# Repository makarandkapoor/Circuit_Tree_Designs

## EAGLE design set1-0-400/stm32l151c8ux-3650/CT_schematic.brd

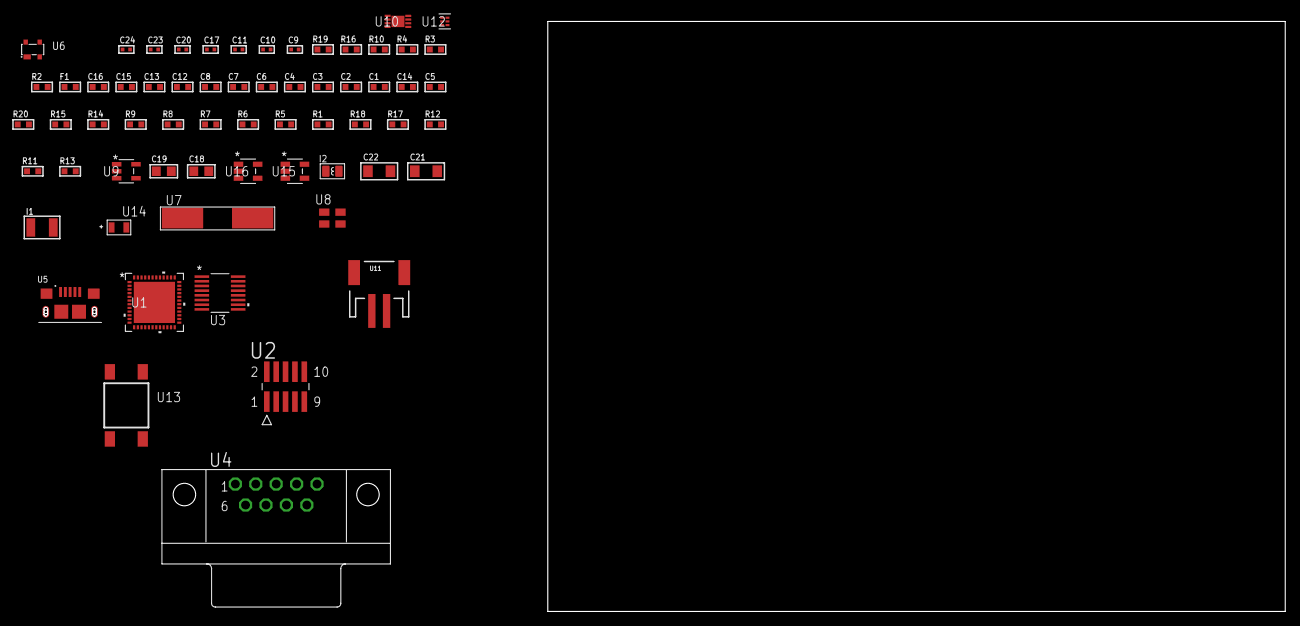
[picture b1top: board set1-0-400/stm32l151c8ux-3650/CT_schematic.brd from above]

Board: 2 copper layers, 168.3 x 80.0 mm, 63 parts (0 on the bottom side), 43 nets, no tracks yet.

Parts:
C1, C2, C3, C4, C6: 1e-07; C0603
C5: 4.7e-06; C0603
C7: 1e-08; C0603
C8, C12, C13, C15, C16: 1e-06; C0603
C9, C10: 1e-11; C0402
C11, C20: 1e-07; C0402
C14: 2.2e-07; C0603
C17, C23, C24: 1e-08; C0402
C18, C19: 1e-05; C0805
C21, C22: 1e-05; C1206
F1: 240.0; L0603
I1: 1e-05; L1210
I2: 3.3e-06; L0806
R1, R5, R6, R7, R8, R9, R14, R15, R20: 10000.0; R0603
R2: 1000.0; R0603
R3: 1600.5; R0603
R4: 4700.0; R0603
R10: 5.0; R0603
R11: 100000.0; R0603
R12: 220000.0; R0603
R13: 1000000.0; R0603
R16: 9100.0; R0603
R17: 680000.0; R0603
R18: 120000.0; R0603
R19: 2000.0; R0603
U1: STM32L151C8U6; UFQFPN48
U2: FTSH-105-01-L-DV-K; SAMTEC_FTSH-105-01-L-DV-K
U3: LTC2804CGN-1#PBF; SSOP-16
U4: 182-009-113R531; 182-009-MALE
U5: 10118193-0001LF; FCI_10118193-0001LF
U6: prtr5v0u2ax; SOT143B
U7: ABLS-25.000MHZ-B2F-T
U8: ASEK-32.768KHz-ECST; ASEK
U9: ltc3406es5; TSOT-23-5
U10: MCP73831T-2ACI/MC; DFN8_2X3MC
U11: S2B-PH-SM4-TB(LF)(SN); JST-2-SMD
U12: TPS3895ADRYR; SON-6
U13: 4-1437565-2; SW_4-1437565-2
U14: Q65110A2395; LGM67K-G1J2-24-Z
U15, U16: nc7sz125m5x; NC7SZ125M5X

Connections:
CLK_CRYSTAL_U1_5: C9.1, U1.5, U7.1
CLK_CRYSTAL_U1_6: C10.1, U1.6, U7.2
CLK_U1_3: U1.3, U8.3
GND: C1.2, C2.2, C3.2, C4.2, C5.2, C6.2, C7.2, C8.2, C9.2, C10.2, C11.2, C12.2, C13.2, C15.2, C16.2, C17.2, C18.2, C19.1, C19.2, C20.2, C21.2, C22.2, C23.2, C24.2, R2.2, R5.2, R9.2, R10.2, R12.2, R16.2, R18.2, R19.2, U1.8, U1.23, U1.35, U1.47, U1.49, U2.3, U2.5, U3.8, U4.5, U5.5, U5.6, U5.7, U5.8, U5.9, U6.1, U8.2, U9.2, U10.6, U10.9, U11.2, U12.2, U14.C, U15.2, U15.3, U16.1, U16.3
INPUT_USBPOWER_5V: C21.1, R20.2, U5.1, U6.4, U10.1, U10.2
NET_U1_1: C6.1, U1.1
NET_U1_7: R4.1, U1.7, U16.4
NET_U1_9: C7.1, C8.1, F1.1, U1.9
NET_U1_44: R5.1, U1.44
NET_U1_45: R3.1, U1.45, U14.A
NET_U1_46: R1.1, U1.46, U13.3, U13.4
NET_U2_9: R10.1, U2.9
NET_U3_6: C12.1, U3.6
NET_U3_7: C14.1, I1.2, U3.7
NET_U3_9: C13.1, U3.9
NET_U3_10: C14.2, U3.10
NET_U3_11: R11.1, U3.11
NET_U4_2: U3.1, U4.2
NET_U4_3: U3.3, U4.3
NET_U4_7: U3.2, U4.7
NET_U4_8: U3.4, U4.8
NET_U9_3: I2.1, U9.3
NET_U9_5: R12.1, R13.1, U9.5
NET_U9_ATNET_3: I2.2, R13.2
NET_U10_5: R20.1, U10.5
NET_U10_8: R19.1, U10.8
NET_U12_1: R15.1, R16.1, U12.1
NET_U12_3: R17.2, R18.1, U12.3
NET_U12_4: R14.1, U12.4, U15.4, U16.2
NET_U13_1: R2.1, U13.1, U13.2
PROC_SYS_JTCK_SWCLK: R9.1, U1.37, U2.4
PROC_SYS_JTDI: R7.1, U1.38, U2.8
PROC_SYS_JTDO_TRACESWO: U1.39, U2.6
PROC_SYS_JTMS_SWDIO: R8.1, U1.34, U2.2
PROC_USART2_CTS: U1.10, U3.13
PROC_USART2_RTS: U1.11, U3.15
PROC_USART2_RX: U1.13, U3.16
PROC_USART2_TX: U1.12, U3.14
PROC_USB_DM: U1.32, U5.2, U6.3
PROC_USB_DP: U1.33, U5.3, U6.2
RST_OUT_U2_JTAG_RST_B: R6.1, U2.10, U15.1
VCC_S1_3V7: C18.1, C22.1, U9.4, U10.3, U10.4, U11.1
VCC_TIER1_3V3: C1.1, C2.1, C3.1, C4.1, C5.1, C11.1, C15.1, C16.1, C17.1, C19.2, C20.1, C23.1, C24.1, F1.2, I1.1, I2.2, R1.2, R3.2, R4.2, R6.2, R7.2, R8.2, R11.2, R13.2, R14.2, R15.2, R17.1, U1.24, U1.36, U1.48, U2.1, U3.5, U3.12, U8.4, U12.6, U15.5, U16.5

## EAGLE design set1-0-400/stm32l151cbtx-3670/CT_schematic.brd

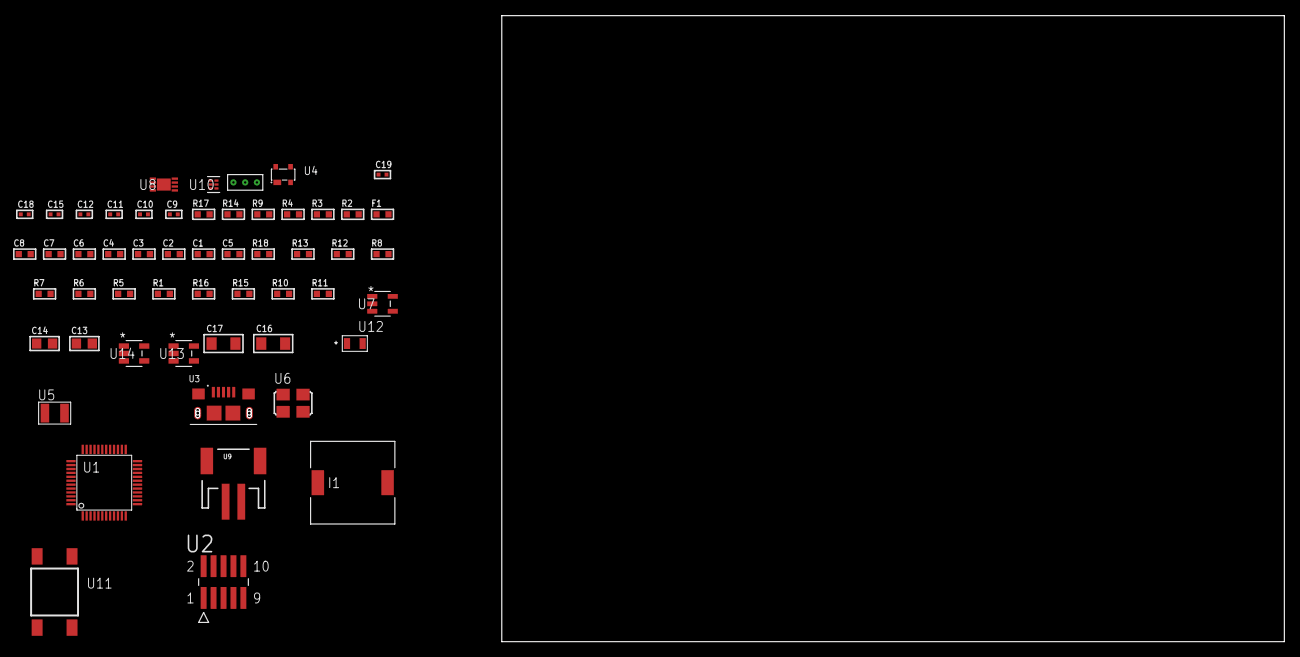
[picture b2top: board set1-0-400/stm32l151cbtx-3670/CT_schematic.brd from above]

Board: 2 copper layers, 54 parts (0 on the bottom side), 31 nets, no tracks yet.

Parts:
C1, C2, C3, C4, C6: 1e-07; C0603
C5: 4.7e-06; C0603
C7: 1e-08; C0603
C8: 1e-06; C0603
C9, C10: 1e-11; C0402
C11, C15: 1e-07; C0402
C12, C18, C19: 1e-08; C0402
C13, C14: 1e-05; C0805
C16, C17: 1e-05; C1206
F1: 240.0; L0603
I1: 3.8e-06; DR1040
R1, R5, R6, R7, R8, R12, R13, R18: 10000.0; R0603
R2: 1000.0; R0603
R3: 1600.5; R0603
R4: 4700.0; R0603
R9: 5.0; R0603
R10: 220000.0; R0603
R11: 1000000.0; R0603
R14: 9100.0; R0603
R15: 680000.0; R0603
R16: 120000.0; R0603
R17: 2000.0; R0603
U1: STM32L151CBT6; LQFP48
U2: FTSH-105-01-L-DV-K; SAMTEC_FTSH-105-01-L-DV-K
U3: 10118193-0001LF; FCI_10118193-0001LF
U4: prtr5v0u2ax; SOT143B
U5: ABS07-32.768KHZ-7-T
U6: ASFL1-25MHZ-NCS; ASFL1
U7: ltc3406es5; TSOT-23-5
U8: MCP73831T-2ACI/MC; DFN8_2X3MC
U9: S2B-PH-SM4-TB(LF)(SN); JST-2-SMD
U10: TPS3895ADRYR; SON-6
U11: 4-1437565-2; SW_4-1437565-2
U12: Q65110A2395; LGM67K-G1J2-24-Z
U13, U14: nc7sz125m5x; NC7SZ125M5X
U15: Dummy; DUMMY_PACKAGE_112

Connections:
CLK_CRYSTAL_U1_3: C9.1, U1.3, U5.1
CLK_CRYSTAL_U1_4: C10.1, U1.4, U5.2
CLK_U1_5: U1.5, U6.3
GND: C1.2, C2.2, C3.2, C4.2, C5.2, C6.2, C7.2, C8.2, C9.2, C10.2, C11.2, C12.2, C13.2, C14.1, C14.2, C15.2, C16.2, C17.2, C18.2, C19.2, R2.2, R5.2, R9.2, R10.2, R14.2, R16.2, R17.2, U1.8, U1.23, U1.35, U1.47, U2.3, U2.5, U3.5, U3.6, U3.7, U3.8, U3.9, U4.1, U6.2, U7.2, U8.6, U8.9, U9.2, U10.2, U12.C, U13.2, U13.3, U14.1, U14.3, U15.1
INPUT_USBPOWER_5V: C16.1, R18.2, U3.1, U4.4, U8.1, U8.2
NET_U1_1: C6.1, U1.1
NET_U1_7: R4.1, U1.7, U14.4
NET_U1_9: C7.1, C8.1, F1.1, U1.9
NET_U1_44: R5.1, U1.44
NET_U1_45: R3.1, U1.45, U12.A
NET_U1_46: R1.1, U1.46, U11.3, U11.4
NET_U2_9: R9.1, U2.9
NET_U7_3: I1.1, U7.3
NET_U7_5: R10.1, R11.1, U7.5
NET_U7_ATNET_3: I1.2, R11.2
NET_U8_5: R18.1, U8.5
NET_U8_8: R17.1, U8.8
NET_U10_1: R13.1, R14.1, U10.1
NET_U10_3: R15.2, R16.1, U10.3
NET_U10_4: R12.1, U10.4, U13.4, U14.2
NET_U11_1: R2.1, U11.1, U11.2
PROC_PC13_WKUP2: U1.2, U15.2
PROC_PH1_OSC_OUT: U1.6, U15.3
PROC_SYS_JTCK_SWCLK: R7.1, U1.37, U2.4
PROC_SYS_JTDO_TRACESWO: U1.39, U2.6
PROC_SYS_JTMS_SWDIO: R8.1, U1.34, U2.2
PROC_USB_DM: U1.32, U3.2, U4.3
PROC_USB_DP: U1.33, U3.3, U4.2
RST_OUT_U2_JTAG_RST_B: R6.1, U2.10, U13.1
VCC_S1_3V7: C13.1, C17.1, U7.4, U8.3, U8.4, U9.1
VCC_TIER1_3V3: C1.1, C2.1, C3.1, C4.1, C5.1, C11.1, C12.1, C14.2, C15.1, C18.1, C19.1, F1.2, I1.2, R1.2, R3.2, R4.2, R6.2, R7.2, R8.2, R11.2, R12.2, R13.2, R15.1, U1.24, U1.36, U1.48, U2.1, U6.4, U10.6, U13.5, U14.5

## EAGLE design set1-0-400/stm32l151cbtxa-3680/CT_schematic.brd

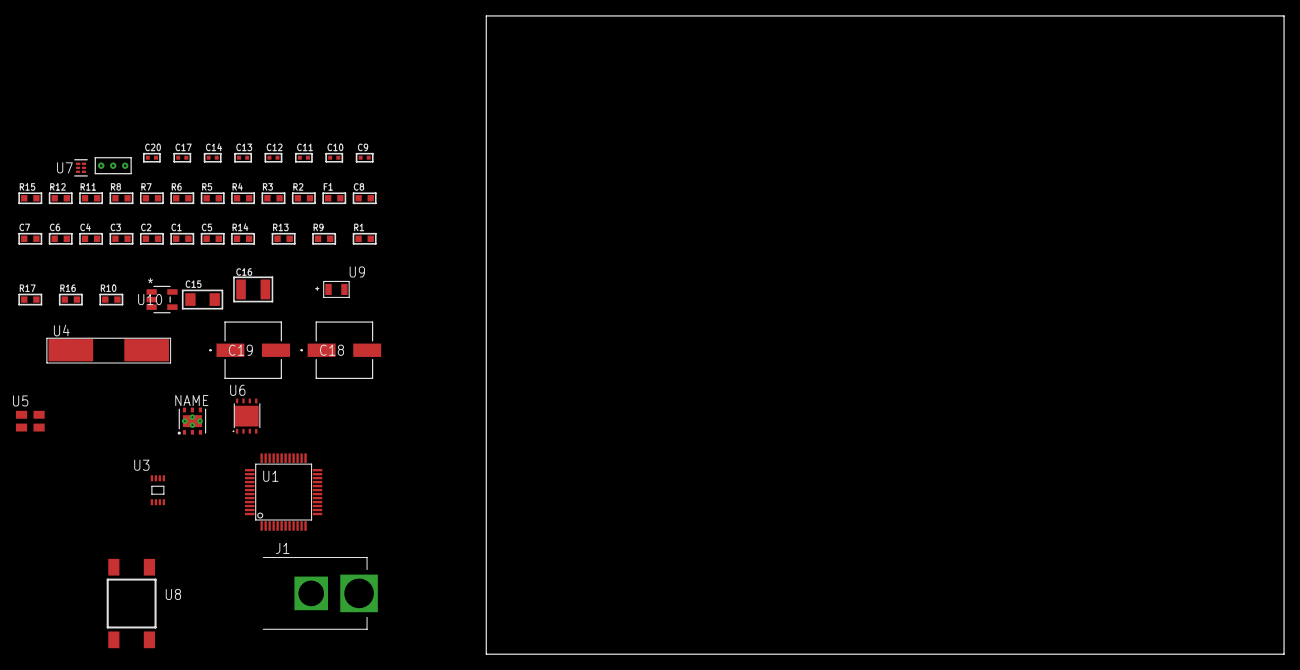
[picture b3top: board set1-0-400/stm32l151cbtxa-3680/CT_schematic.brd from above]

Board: 2 copper layers, 100.0 x 80.0 mm, 50 parts (0 on the bottom side), 25 nets, no tracks yet.

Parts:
C1, C2, C3, C4, C6: 1e-07; C0603
C5: 4.7e-06; C0603
C7: 1e-08; C0603
C8: 1e-06; C0603
C9, C10: 1e-11; C0402
C11, C12, C13, C14, C20: 1e-08; C0402
C15: 1e-05; C1206
C16: 1e-05; C1210
C17: 1e-07; C0402
C18, C19: 0.0001; EXV-9H
F1: 240.0; L0603
J1: PJ-037B; PJ-037B_PACKAGE
R1, R9, R13, R14: 10000.0; R0603
R2, R12: 1000.0; R0603
R3: 1600.5; R0603
R4: 4700.0; R0603
R5, R6, R7, R8: 2200.0; R0603
R10: 100000.0; R0603
R11: 2231.0; R0603
R15: 9100.0; R0603
R16: 680000.0; R0603
R17: 120000.0; R0603
U1: STM32L151CBT6A; LQFP48
U2: HDC1080DMBR; WSON-6
U3: 24AA08T-I/MNY; TDFN-8/6MM
U4: ABLS-25.000MHZ-B2F-T
U5: ASEK-32.768KHz-ECST; ASEK
U6: LP3878SDX-ADJ/NOPB; WSON-8
U7: TPS3895ADRYR; SON-6
U8: 4-1437565-2; SW_4-1437565-2
U9: Q65110A2395; LGM67K-G1J2-24-Z
U10: nc7sz125m5x; NC7SZ125M5X
U11: Dummy; DUMMY_PACKAGE_103

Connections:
CLK_CRYSTAL_U1_5: C9.1, U1.5, U4.1
CLK_CRYSTAL_U1_6: C10.1, U1.6, U4.2
CLK_U1_3: U1.3, U5.3
GND: C1.2, C2.2, C3.2, C4.2, C5.2, C6.2, C7.2, C8.2, C9.2, C10.2, C11.2, C12.2, C13.2, C14.2, C15.2, C16.2, C17.2, C18.2, C19.2, C20.2, J1.2, R2.2, R9.2, R12.2, R15.2, R17.2, U1.8, U1.23, U1.35, U1.47, U2.2, U2.PAD, U3.4, U3.7, U5.2, U6.3, U6.PAD, U7.2, U9.C, U10.1, U10.3, U11.1
NET_U1_1: C6.1, U1.1
NET_U1_7: R4.1, U1.7, U10.4
NET_U1_9: C7.1, C8.1, F1.1, U1.9
NET_U1_21: R7.1, U1.21, U3.6
NET_U1_22: R8.1, U1.22, U3.5
NET_U1_42: R5.1, U1.42, U2.6
NET_U1_43: R6.1, U1.43, U2.1
NET_U1_44: R9.1, U1.44
NET_U1_45: R3.1, U1.45, U9.A
NET_U1_46: R1.1, U1.46, U8.3, U8.4
NET_U6_1: C14.1, U6.1
NET_U6_6: R11.2, R12.1, U6.6
NET_U6_8: R10.1, U6.8
NET_U7_1: R14.1, R15.1, U7.1
NET_U7_3: R16.2, R17.1, U7.3
NET_U7_4: R13.1, U7.4, U10.2
NET_U8_1: R2.1, U8.1, U8.2
PROC_TIM10_CH1: U1.16, U11.2
PROC_TIM11_CH1: U1.17, U11.3
VCC_S1_9V1: C15.1, C18.1, C19.1, J1.1, R10.2, U6.4
VCC_TIER1_3V3: C1.1, C2.1, C3.1, C4.1, C5.1, C11.1, C12.1, C13.1, C16.1, C17.1, C20.1, F1.2, R1.2, R3.2, R4.2, R5.2, R6.2, R7.2, R8.2, R11.1, R13.2, R14.2, R16.1, U1.24, U1.36, U1.48, U2.5, U3.8, U5.4, U6.5, U7.6, U10.5

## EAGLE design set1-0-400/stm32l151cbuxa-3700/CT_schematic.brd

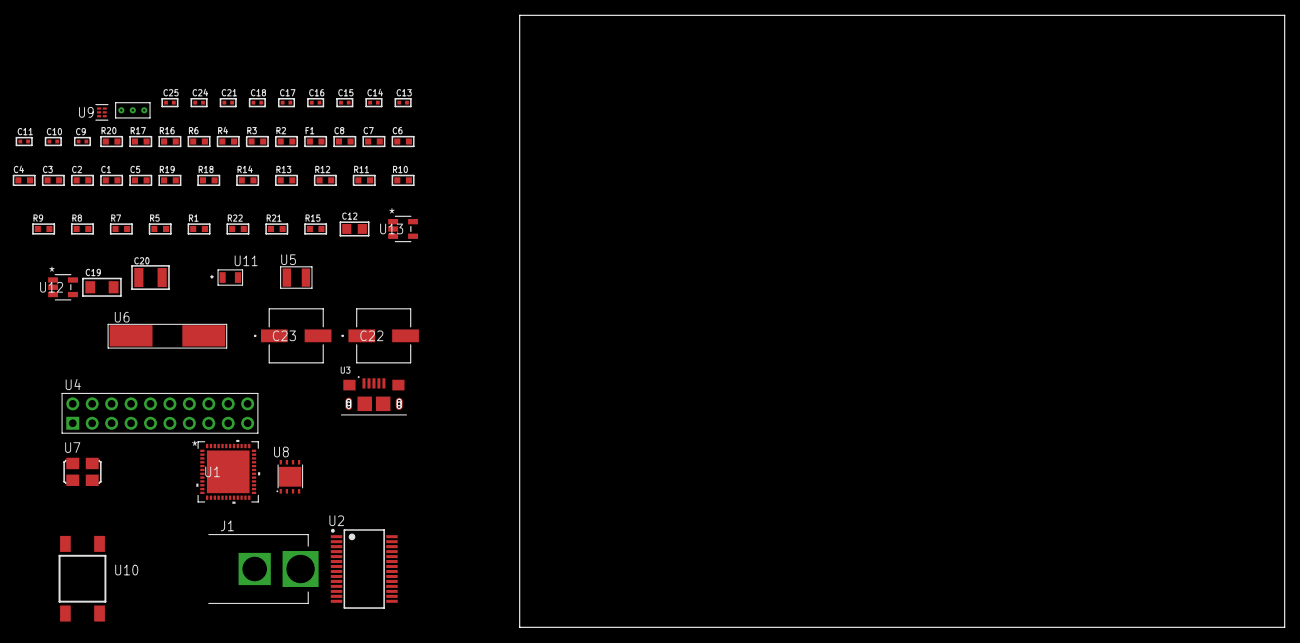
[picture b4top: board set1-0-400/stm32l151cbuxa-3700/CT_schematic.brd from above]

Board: 2 copper layers, 122.6 x 80.0 mm, 63 parts (0 on the bottom side), 40 nets, no tracks yet.

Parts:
C1, C2, C3, C4, C6: 1e-07; C0603
C5: 4.7e-06; C0603
C7: 1e-08; C0603
C8: 1e-06; C0603
C9, C10: 1e-11; C0402
C11, C13, C14, C15, C16, C21: 1e-07; C0402
C12: 4.7e-06; C0805
C17, C18, C24, C25: 1e-08; C0402
C19: 1e-05; C1206
C20: 1e-05; C1210
C22, C23: 0.0001; EXV-9H
F1: 240.0; L0603
J1: PJ-037B; PJ-037B_PACKAGE
R1, R5, R7, R8, R9, R10, R11, R12, R13, R14, R18, R19: 10000.0; R0603
R2, R17: 1000.0; R0603
R3: 1600.5; R0603
R4, R6: 4700.0; R0603
R15: 100000.0; R0603
R16: 2231.0; R0603
R20: 9100.0; R0603
R21: 680000.0; R0603
R22: 120000.0; R0603
U1: STM32L151CBU6A; UFQFPN48
U2: FT232RL-REEL; SSOP-28
U3: 10118193-0001LF; FCI_10118193-0001LF
U4: TST-110-05-T-D-RA
U5: ABS07-32.768KHZ-7-T
U6: ABLS-12.000MHZ-B4-T
U7: ASFL1-25MHZ-NCS; ASFL1
U8: LP3878SDX-ADJ/NOPB; WSON-8
U9: TPS3895ADRYR; SON-6
U10: 4-1437565-2; SW_4-1437565-2
U11: Q65110A2395; LGM67K-G1J2-24-Z
U12, U13: nc7sz125m5x; NC7SZ125M5X
U14: Dummy; DUMMY_PACKAGE_130

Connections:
CLK_CRYSTAL_U1_3: C9.1, U1.3, U5.1
CLK_CRYSTAL_U1_4: C10.1, U1.4, U5.2
CLK_CRYSTAL_U2_27: U2.27, U6.1
CLK_CRYSTAL_U2_28: U2.28, U6.2
CLK_U1_5: U1.5, U7.3
GND: C1.2, C2.2, C3.2, C4.2, C5.2, C6.2, C7.2, C8.2, C9.2, C10.2, C11.2, C12.2, C13.2, C14.2, C15.2, C16.2, C17.2, C18.2, C19.2, C20.2, C21.2, C22.2, C23.2, C24.2, C25.2, J1.2, R2.2, R5.2, R8.2, R14.2, R17.2, R20.2, R22.2, U1.8, U1.23, U1.35, U1.47, U1.49, U2.7, U2.18, U2.21, U2.25, U2.26, U3.5, U3.6, U3.7, U3.8, U3.9, U4.4, U4.6, U4.8, U4.10, U4.12, U4.14, U4.16, U4.18, U4.20, U7.2, U8.3, U8.PAD, U9.2, U11.C, U12.2, U12.3, U13.1, U13.3, U14.1
NET_U1_1: C6.1, U1.1
NET_U1_7: R4.1, U1.7, U13.4
NET_U1_9: C7.1, C8.1, F1.1, U1.9
NET_U1_44: R5.1, U1.44
NET_U1_45: R3.1, U1.45, U11.A
NET_U1_46: R1.1, U1.46, U10.3, U10.4
NET_U2_14: R7.1, U2.14
NET_U2_17: C13.1, U2.17
NET_U2_19: R8.1, U2.19
NET_U3_1: R6.1, U3.1
NET_U3_2: U2.16, U3.2
NET_U3_3: U2.15, U3.3
NET_U4_19: R14.1, U4.19
NET_U8_1: C18.1, U8.1
NET_U8_6: R16.2, R17.1, U8.6
NET_U8_8: R15.1, U8.8
NET_U9_1: R19.1, R20.1, U9.1
NET_U9_3: R21.2, R22.1, U9.3
NET_U9_4: R18.1, U9.4, U12.4, U13.2
NET_U10_1: R2.1, U10.1, U10.2
PROC_ADC_IN19: U1.26, U14.3
PROC_ADC_IN20: U1.27, U14.2
PROC_SYS_JTCK_SWCLK: R12.1, U1.37, U4.9
PROC_SYS_JTDI: R10.1, U1.38, U4.5
PROC_SYS_JTDO_TRACESWO: U1.39, U4.13
PROC_SYS_JTMS_SWDIO: R11.1, U1.34, U4.7
PROC_SYS_JTRST: R9.1, U1.40, U4.3
PROC_USART1_CTS: U1.32, U2.3
PROC_USART1_RTS: U1.33, U2.11
PROC_USART1_RX: U1.31, U2.1
PROC_USART1_TX: U1.30, U2.5
RST_OUT_U4_SRESET_B: R13.1, U4.15, U12.1
VCC_S1_8V5: C19.1, C22.1, C23.1, J1.1, R15.2, U8.4
VCC_TIER1_3V3: C1.1, C2.1, C3.1, C4.1, C5.1, C11.1, C12.1, C14.1, C15.1, C16.1, C17.1, C20.1, C21.1, C24.1, C25.1, F1.2, R1.2, R3.2, R4.2, R7.2, R9.2, R10.2, R11.2, R12.2, R13.2, R16.1, R18.2, R19.2, R21.1, U1.24, U1.36, U1.48, U2.4, U2.20, U4.1, U4.2, U7.4, U8.5, U9.6, U12.5, U13.5

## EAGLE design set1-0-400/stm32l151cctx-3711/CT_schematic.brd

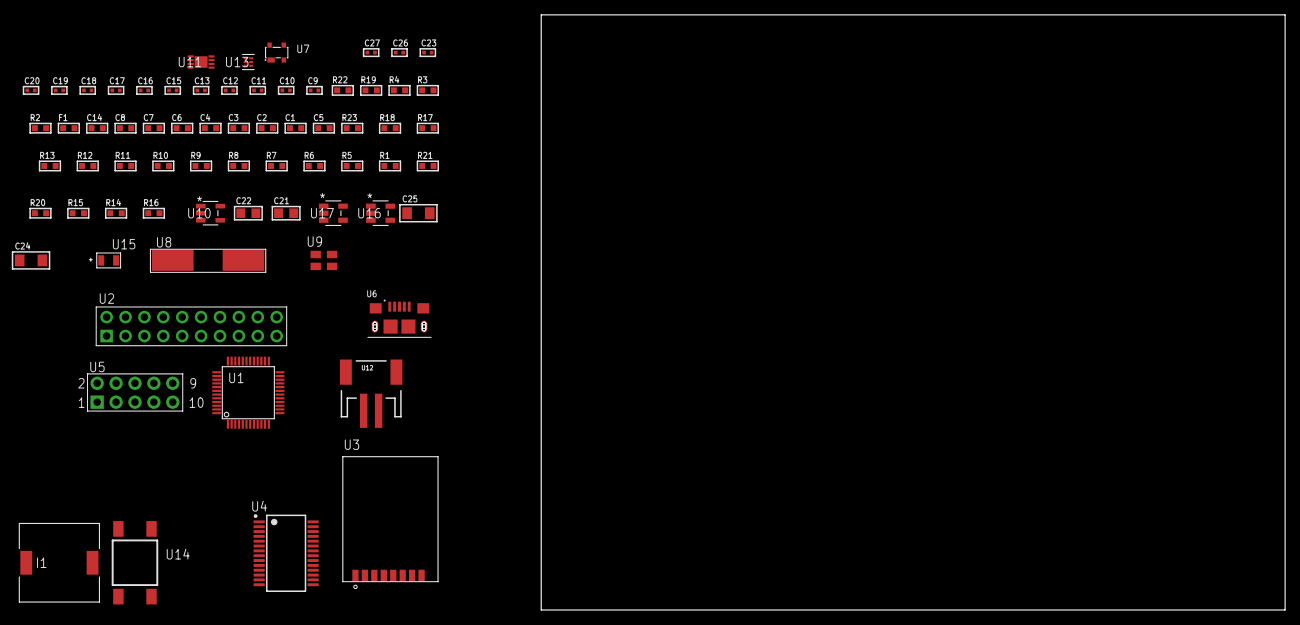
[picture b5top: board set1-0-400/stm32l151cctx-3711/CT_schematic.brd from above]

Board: 2 copper layers, 122.6 x 80.0 mm, 69 parts (0 on the bottom side), 51 nets, no tracks yet.

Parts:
C1, C2, C3, C4, C6: 1e-07; C0603
C5: 4.7e-06; C0603
C7: 1e-08; C0603
C8, C14: 1e-06; C0603
C9, C10: 1e-11; C0402
C11, C12, C13, C15, C16, C17, C18, C19, C23: 1e-07; C0402
C20, C26, C27: 1e-08; C0402
C21, C22: 1e-05; C0805
C24, C25: 1e-05; C1206
F1: 240.0; L0603
I1: 2.5e-06; DR1040
R1, R5, R6, R7, R8, R9, R10, R11, R12, R13, R17, R18, R23: 10000.0; R0603
R2: 1000.0; R0603
R3: 1600.5; R0603
R4: 4700.0; R0603
R14: 100000.0; R0603
R15: 220000.0; R0603
R16: 1000000.0; R0603
R19: 9100.0; R0603
R20: 680000.0; R0603
R21: 120000.0; R0603
R22: 2000.0; R0603
U1: STM32L151CCT6; LQFP48
U2: TST-110-05-T-D-RA
U3: RFM75-S
U4: ST3241EBPR; SSOP-28
U5: HTSS-105-01-G-D
U6: 10118193-0001LF; FCI_10118193-0001LF
U7: prtr5v0u2ax; SOT143B
U8: ABLS-25.000MHZ-B2F-T
U9: ASEK-32.768KHz-ECST; ASEK
U10: ltc3406es5; TSOT-23-5
U11: MCP73831T-2ACI/MC; DFN8_2X3MC
U12: S2B-PH-SM4-TB(LF)(SN); JST-2-SMD
U13: TPS3895ADRYR; SON-6
U14: 4-1437565-2; SW_4-1437565-2
U15: Q65110A2395; LGM67K-G1J2-24-Z
U16, U17: nc7sz125m5x; NC7SZ125M5X

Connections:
CLK_CRYSTAL_U1_5: C9.1, U1.5, U8.1
CLK_CRYSTAL_U1_6: C10.1, U1.6, U8.2
CLK_U1_3: U1.3, U9.3
GND: C1.2, C2.2, C3.2, C4.2, C5.2, C6.2, C7.2, C8.2, C9.2, C10.2, C11.2, C12.2, C13.2, C14.2, C15.2, C18.2, C19.2, C20.2, C21.2, C22.1, C22.2, C23.2, C24.2, C25.2, C26.2, C27.2, R2.2, R5.2, R11.2, R15.2, R19.2, R21.2, R22.2, U1.8, U1.23, U1.35, U1.47, U2.4, U2.6, U2.8, U2.10, U2.12, U2.14, U2.16, U2.18, U2.20, U3.1, U4.23, U4.25, U5.9, U6.5, U6.6, U6.7, U6.8, U6.9, U7.1, U9.2, U10.2, U11.6, U11.9, U12.2, U13.2, U15.C, U16.2, U16.3, U17.1, U17.3
INPUT_USBPOWER_5V: C24.1, R23.2, U6.1, U7.4, U11.1, U11.2
NET_U1_1: C6.1, U1.1
NET_U1_7: R4.1, U1.7, U17.4
NET_U1_9: C7.1, C8.1, F1.1, U1.9
NET_U1_44: R5.1, U1.44
NET_U1_45: R3.1, U1.45, U15.A
NET_U1_46: R1.1, U1.46, U14.3, U14.4
NET_U2_19: R11.1, U2.19
NET_U3_3: R12.1, U3.3
NET_U4_1: C17.1, U4.1
NET_U4_2: C17.2, U4.2
NET_U4_3: C19.1, U4.3
NET_U4_22: R14.1, U4.22
NET_U4_24: C16.2, U4.24
NET_U4_27: C18.1, U4.27
NET_U4_28: C16.1, U4.28
NET_U5_3: U4.4, U5.3
NET_U5_4: U4.5, U5.4
NET_U5_5: U4.9, U5.5
NET_U5_6: U4.10, U5.6
NET_U10_3: I1.1, U10.3
NET_U10_5: R15.1, R16.1, U10.5
NET_U10_ATNET_3: I1.2, R16.2
NET_U11_5: R23.1, U11.5
NET_U11_8: R22.1, U11.8
NET_U13_1: R18.1, R19.1, U13.1
NET_U13_3: R20.2, R21.1, U13.3
NET_U13_4: R17.1, U13.4, U16.4, U17.2
NET_U14_1: R2.1, U14.1, U14.2
PROC_SPI1_MISO: U1.16, U3.7
PROC_SPI1_MOSI: U1.17, U3.6
PROC_SPI1_NSS: R13.1, U1.14, U3.4
PROC_SPI1_SCK: U1.15, U3.5
PROC_SYS_JTCK_SWCLK: R9.1, U1.37, U2.9
PROC_SYS_JTDI: R7.1, U1.38, U2.5
PROC_SYS_JTDO_TRACESWO: U1.39, U2.13
PROC_SYS_JTMS_SWDIO: R8.1, U1.34, U2.7
PROC_SYS_JTRST: R6.1, U1.40, U2.3
PROC_USART2_CTS: U1.10, U4.13
PROC_USART2_RTS: U1.11, U4.18
PROC_USART2_RX: U1.13, U4.19
PROC_USART2_TX: U1.12, U4.14
PROC_USB_DM: U1.32, U6.2, U7.3
PROC_USB_DP: U1.33, U6.3, U7.2
RST_OUT_U2_SRESET_B: R10.1, U2.15, U16.1
VCC_S1_3V7: C21.1, C25.1, U10.4, U11.3, U11.4, U12.1
VCC_TIER1_3V3: C1.1, C2.1, C3.1, C4.1, C5.1, C11.1, C12.1, C13.1, C14.1, C15.1, C20.1, C22.2, C23.1, C26.1, C27.1, F1.2, I1.2, R1.2, R3.2, R4.2, R6.2, R7.2, R8.2, R9.2, R10.2, R12.2, R13.2, R14.2, R16.2, R17.2, R18.2, R20.1, U1.24, U1.36, U1.48, U2.1, U2.2, U3.2, U4.26, U9.4, U13.6, U16.5, U17.5

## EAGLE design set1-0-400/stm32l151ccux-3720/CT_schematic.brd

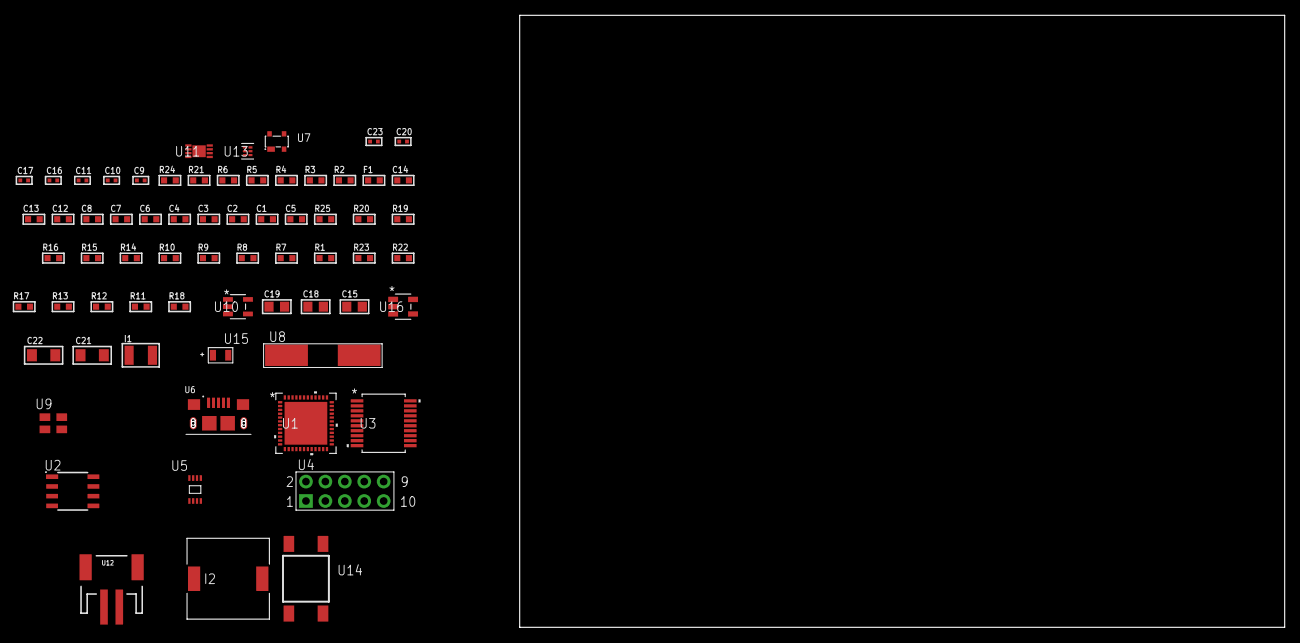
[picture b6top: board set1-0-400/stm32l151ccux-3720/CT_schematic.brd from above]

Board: 2 copper layers, 67 parts (0 on the bottom side), 51 nets, no tracks yet.

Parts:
C1, C2, C3, C4, C6: 1e-07; C0603
C5: 4.7e-06; C0603
C7: 1e-08; C0603
C8, C12, C13, C14: 1e-06; C0603
C9, C10: 1e-11; C0402
C11, C16, C17, C23: 1e-08; C0402
C15: 4.7e-06; C0805
C18, C19: 1e-05; C0805
C20: 1e-07; C0402
C21, C22: 1e-05; C1206
F1: 240.0; L0603
I1: 1.5e-05; L1210
I2: 2.5e-06; DR1040
R1, R7, R8, R9, R10, R14, R15, R16, R19, R20, R25: 10000.0; R0603
R2: 1000.0; R0603
R3: 1600.5; R0603
R4: 4700.0; R0603
R5, R6: 2200.0; R0603
R11, R12, R13: 100000.0; R0603
R17: 220000.0; R0603
R18: 1000000.0; R0603
R21: 9100.0; R0603
R22: 680000.0; R0603
R23: 120000.0; R0603
R24: 2000.0; R0603
U1: STM32L151CCU6; UFQFPN48
U2: AT25020B-SSHL-T; SOIC-8
U3: MAX3218EAP+T; SSOP-20
U4: HTSS-105-01-G-D
U5: 24AA32AT-I/MNY; TDFN-8/6MM
U6: 10118193-0001LF; FCI_10118193-0001LF
U7: prtr5v0u2ax; SOT143B
U8: ABLS-25.000MHZ-B2F-T
U9: ASEK-32.768KHz-ECST; ASEK
U10: ltc3406es5; TSOT-23-5
U11: MCP73831T-2ACI/MC; DFN8_2X3MC
U12: S2B-PH-SM4-TB(LF)(SN); JST-2-SMD
U13: TPS3895ADRYR; SON-6
U14: 4-1437565-2; SW_4-1437565-2
U15: Q65110A2395; LGM67K-G1J2-24-Z
U16: nc7sz125m5x; NC7SZ125M5X

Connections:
CLK_CRYSTAL_U1_5: C9.1, U1.5, U8.1
CLK_CRYSTAL_U1_6: C10.1, U1.6, U8.2
CLK_U1_3: U1.3, U9.3
GND: C1.2, C2.2, C3.2, C4.2, C5.2, C6.2, C7.2, C8.2, C9.2, C10.2, C11.2, C12.2, C13.2, C14.2, C16.2, C17.2, C18.2, C19.1, C19.2, C20.2, C21.2, C22.2, C23.2, R2.2, R7.2, R14.2, R17.2, R21.2, R23.2, R24.2, U1.8, U1.23, U1.35, U1.47, U1.49, U2.4, U3.5, U3.17, U3.20, U4.9, U5.4, U6.5, U6.6, U6.7, U6.8, U6.9, U7.1, U9.2, U10.2, U11.6, U11.9, U12.2, U13.2, U15.C, U16.1, U16.3
INPUT_USBPOWER_5V: C21.1, R25.2, U6.1, U7.4, U11.1, U11.2
NET_U1_1: C6.1, U1.1
NET_U1_7: R4.1, U1.7, U16.4
NET_U1_9: C7.1, C8.1, F1.1, U1.9
NET_U1_42: R5.1, U1.42, U5.6
NET_U1_43: R6.1, U1.43, U5.5
NET_U1_44: R7.1, U1.44
NET_U1_45: R3.1, U1.45, U15.A
NET_U1_46: R1.1, U1.46, U14.3, U14.4
NET_U2_3: R8.1, U2.3
NET_U2_7: R10.1, U2.7
NET_U3_1: I1.1, U3.1
NET_U3_2: R11.1, U3.2
NET_U3_3: R12.1, U3.3
NET_U3_4: R13.1, U3.4
NET_U3_15: C14.1, U3.15
NET_U3_16: C15.2, U3.16
NET_U3_18: C15.1, U3.18
NET_U3_19: C13.1, U3.19
NET_U4_3: U3.12, U4.3
NET_U4_4: U3.11, U4.4
NET_U4_5: U3.14, U4.5
NET_U4_6: U3.13, U4.6
NET_U5_1: R14.1, U5.1
NET_U5_2: R15.1, U5.2
NET_U5_3: R16.1, U5.3
NET_U10_3: I2.1, U10.3
NET_U10_5: R17.1, R18.1, U10.5
NET_U10_ATNET_3: I2.2, R18.2
NET_U11_5: R25.1, U11.5
NET_U11_8: R24.1, U11.8
NET_U13_1: R20.1, R21.1, U13.1
NET_U13_3: R22.2, R23.1, U13.3
NET_U13_4: R19.1, U13.4, U16.2
NET_U14_1: R2.1, U14.1, U14.2
PROC_SPI1_MISO: U1.16, U2.2
PROC_SPI1_MOSI: U1.17, U2.5
PROC_SPI1_NSS: R9.1, U1.14, U2.1
PROC_SPI1_SCK: U1.15, U2.6
PROC_USART2_CTS: U1.10, U3.8
PROC_USART2_RTS: U1.11, U3.10
PROC_USART2_RX: U1.13, U3.9
PROC_USART2_TX: U1.12, U3.7
PROC_USB_DM: U1.32, U6.2, U7.3
PROC_USB_DP: U1.33, U6.3, U7.2
VCC_S1_3V7: C18.1, C22.1, U10.4, U11.3, U11.4, U12.1
VCC_TIER1_3V3: C1.1, C2.1, C3.1, C4.1, C5.1, C11.1, C12.1, C16.1, C17.1, C19.2, C20.1, C23.1, F1.2, I1.2, I2.2, R1.2, R3.2, R4.2, R5.2, R6.2, R8.2, R9.2, R10.2, R11.2, R12.2, R13.2, R15.2, R16.2, R18.2, R19.2, R20.2, R22.1, U1.24, U1.36, U1.48, U2.8, U3.6, U5.7, U5.8, U9.4, U13.6, U16.5

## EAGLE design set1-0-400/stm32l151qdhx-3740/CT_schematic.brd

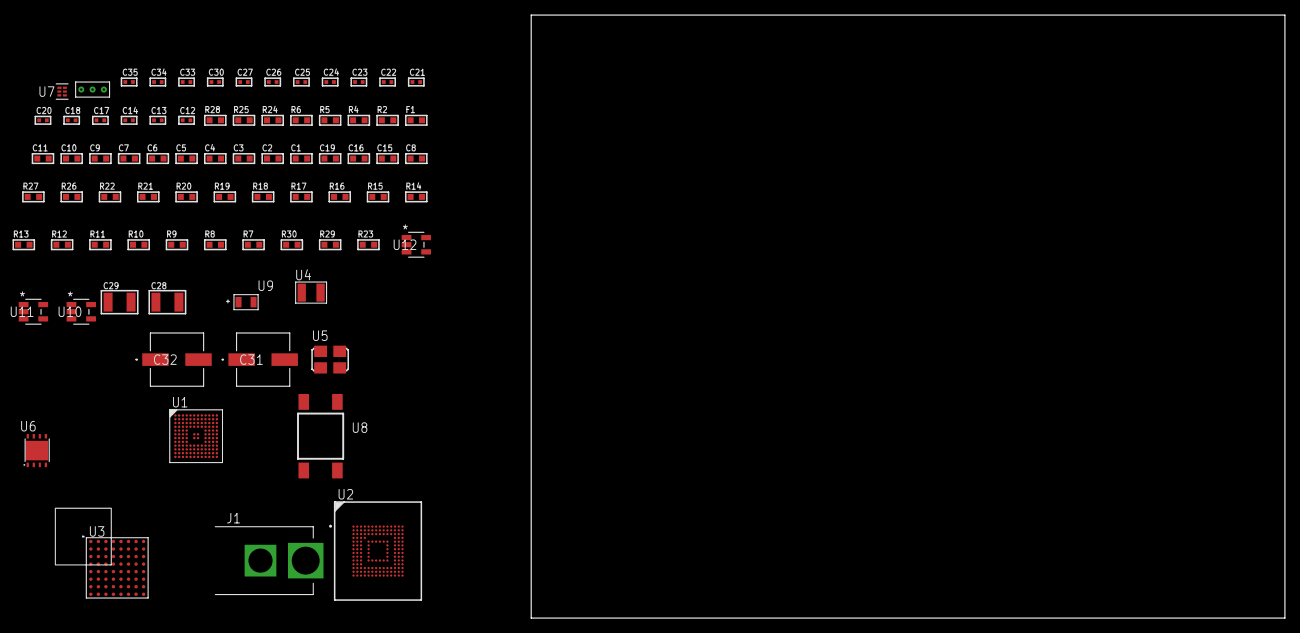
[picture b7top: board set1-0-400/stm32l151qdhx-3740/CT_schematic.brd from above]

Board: 2 copper layers, 100.0 x 80.0 mm, 78 parts (0 on the bottom side), 71 nets, no tracks yet.

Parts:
C1, C2, C3, C4, C5, C6, C7, C9: 1e-07; C0603
C8: 4.7e-06; C0603
C10: 1e-08; C0603
C11: 1e-06; C0603
C12, C13: 1e-11; C0402
C14, C17, C18, C20, C22, C24, C30: 1e-07; C0402
C15, C16, C19: 2.2e-06; C0603
C21, C23, C25, C26, C27, C33, C34, C35: 1e-08; C0402
C28, C29: 1e-05; C1210
C31, C32: 0.0001; EXV-9H
F1: 240.0; L0603
J1: PJ-037B; PJ-037B_PACKAGE
R2, R25: 1000.0; R0603
R4, R5, R6: 4700.0; R0603
R7, R18, R19, R20, R21, R22, R26, R27: 10000.0; R0603
R8, R9, R10, R11, R12, R13, R14, R15, R16, R17: 34000.0; R0603
R23: 100000.0; R0603
R24: 2231.0; R0603
R28: 9100.0; R0603
R29: 680000.0; R0603
R30: 120000.0; R0603
U1: STM32L151QDH6; UFBGA132
U2: mtfc4gmcdm; TFBGA-153
U3: PC28F512P33BFD
U4: ABS07-32.768KHZ-7-T
U5: ASFL1-25MHZ-NCS; ASFL1
U6: LP3878SDX-ADJ/NOPB; WSON-8
U7: TPS3895ADRYR; SON-6
U8: 4-1437565-2; SW_4-1437565-2
U9: Q65110A2395; LGM67K-G1J2-24-Z
U10, U11, U12: nc7sz125m5x; NC7SZ125M5X
U13: Dummy; DUMMY_PACKAGE_176

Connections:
CLK_CRYSTAL_U1_D1: C12.1, U1.D1, U4.1
CLK_CRYSTAL_U1_E1: C13.1, U1.E1, U4.2
CLK_U1_F1: U1.F1, U5.3
GND: C1.2, C2.2, C3.2, C4.2, C5.2, C6.2, C7.2, C8.2, C9.2, C10.2, C11.2, C12.2, C13.2, C14.2, C15.2, C16.2, C17.2, C18.2, C19.2, C20.2, C21.2, C22.2, C23.2, C24.2, C25.2, C26.2, C27.2, C28.2, C29.2, C30.2, C31.2, C32.2, C33.2, C34.2, C35.2, J1.2, R2.2, R7.2, R25.2, R28.2, R30.2, U1.D3, U1.E3, U1.F2, U1.F6, U1.F7, U1.F11, U1.F12, U1.J1, U2.C4, U2.E7, U2.G5, U2.H10, U2.K8, U2.N2, U2.N5, U2.P4, U2.P6, U3.B2, U3.H2, U3.H4, U3.H6, U5.2, U6.3, U6.PAD, U7.2, U9.C, U10.1, U10.3, U11.1, U11.3, U12.1, U12.3, U13.1
NET_U1_A4: R7.1, U1.A4
NET_U1_E2: C9.1, U1.E2
NET_U1_H2: R6.1, U1.H2, U12.4
NET_U1_M1: C10.1, C11.1, F1.1, U1.L1, U1.M1
NET_U1_M6: U8.3, U8.4
NET_U2_C2: C16.1, C17.1, U2.C2
NET_U2_K5: R4.1, U2.K5, U10.4
NET_U3_A4: C24.1, C25.1, U3.A4
NET_U3_C6: R21.1, U3.C6
NET_U3_D4: R5.1, U3.D4, U11.4
NET_U6_1: C27.1, U6.1
NET_U6_6: R24.2, R25.1, U6.6
NET_U6_8: R23.1, U6.8
NET_U7_1: R27.1, R28.1, U7.1
NET_U7_3: R29.2, R30.1, U7.3
NET_U7_4: R26.1, U7.4, U10.2, U11.2, U12.2
NET_U8_1: R2.1, U8.1, U8.2
PROC_ADC_IN20: U1.K11, U13.2
PROC_ADC_IN28: U1.G4, U13.3
PROC_FSMC_A6: U1.J7, U3.C2
PROC_FSMC_A7: U1.K7, U3.A3
PROC_FSMC_A8: U1.J8, U3.B3
PROC_FSMC_A9: U1.J9, U3.C3
PROC_FSMC_A10: U1.H9, U3.D3
PROC_FSMC_A11: U1.G9, U3.C4
PROC_FSMC_A12: U1.G10, U3.A5
PROC_FSMC_A13: U1.F9, U3.B5
PROC_FSMC_A14: U1.F10, U3.C5
PROC_FSMC_A16: U1.J11, U3.D8
PROC_FSMC_A17: U1.J10, U3.A7
PROC_FSMC_A18: U1.H12, U3.B7
PROC_FSMC_A19: U1.A1, U3.C7
PROC_FSMC_A20: U1.B1, U3.C8
PROC_FSMC_A21: U1.C2, U3.A8
PROC_FSMC_A23: U1.B2, U3.H8
PROC_FSMC_CLK: U1.B8, U3.E6
PROC_FSMC_D0: U1.H11, U3.F2
PROC_FSMC_D1: U1.H10, U3.E2
PROC_FSMC_D2: U1.C9, U3.G3
PROC_FSMC_D3: U1.B9, U3.E4
PROC_FSMC_D4: U1.M7, U3.E5
PROC_FSMC_D5: U1.L7, U3.G5
PROC_FSMC_D6: U1.M8, U3.G6
PROC_FSMC_D7: U1.L8, U3.H7
PROC_FSMC_D8: U1.M9, U3.E1
PROC_FSMC_D9: U1.L9, U3.E3
PROC_FSMC_D10: U1.M10, U3.F3
PROC_FSMC_D11: U1.M11, U3.F4
PROC_FSMC_D12: U1.M12, U3.F5
PROC_FSMC_D13: U1.K9, U3.H5
PROC_FSMC_NE2: R19.1, U1.D9, U3.B4
PROC_FSMC_NL: R18.1, U1.B4, U3.F6
PROC_FSMC_NOE: R20.1, U1.B7, U3.F8
PROC_FSMC_NWAIT: U1.B6, U3.F7
PROC_FSMC_NWE: R22.1, U1.A6, U3.G8
PROC_SDIO_CK: R17.1, U1.B10, U2.M6
PROC_SDIO_CMD: R16.1, U1.C8, U2.M5
PROC_SDIO_D0: R8.1, U1.E10, U2.A3
PROC_SDIO_D1: R9.1, U1.D12, U2.A4
PROC_SDIO_D2: R10.1, U1.B11, U2.A5
PROC_SDIO_D3: R11.1, U1.C10, U2.B2
PROC_SDIO_D4: R12.1, U1.A3, U2.B3
PROC_SDIO_D5: R13.1, U1.B3, U2.B4
PROC_SDIO_D6: R14.1, U1.E12, U2.B5
PROC_SDIO_D7: R15.1, U1.E11, U2.B6
VCC_S1_13V6: C28.1, C31.1, C32.1, J1.1, R23.2, U6.4
VCC_TIER1_3V3: C1.1, C2.1, C3.1, C4.1, C5.1, C6.1, C7.1, C8.1, C14.1, C15.1, C18.1, C19.1, C20.1, C21.1, C22.1, C23.1, C26.1, C29.1, C30.1, C33.1, C34.1, C35.1, F1.2, R4.2, R5.2, R6.2, R8.2, R9.2, R10.2, R11.2, R12.2, R13.2, R14.2, R15.2, R16.2, R17.2, R18.2, R19.2, R20.2, R21.2, R22.2, R24.1, R26.2, R27.2, R29.1, U1.C4, U1.G2, U1.G6, U1.G7, U1.G11, U1.G12, U1.H3, U2.C6, U2.E6, U2.F5, U2.J10, U2.K9, U2.M4, U2.N4, U2.P3, U2.P5, U3.A6, U3.D5, U3.D6, U3.G4, U3.H3, U5.4, U6.5, U7.6, U10.5, U11.5, U12.5

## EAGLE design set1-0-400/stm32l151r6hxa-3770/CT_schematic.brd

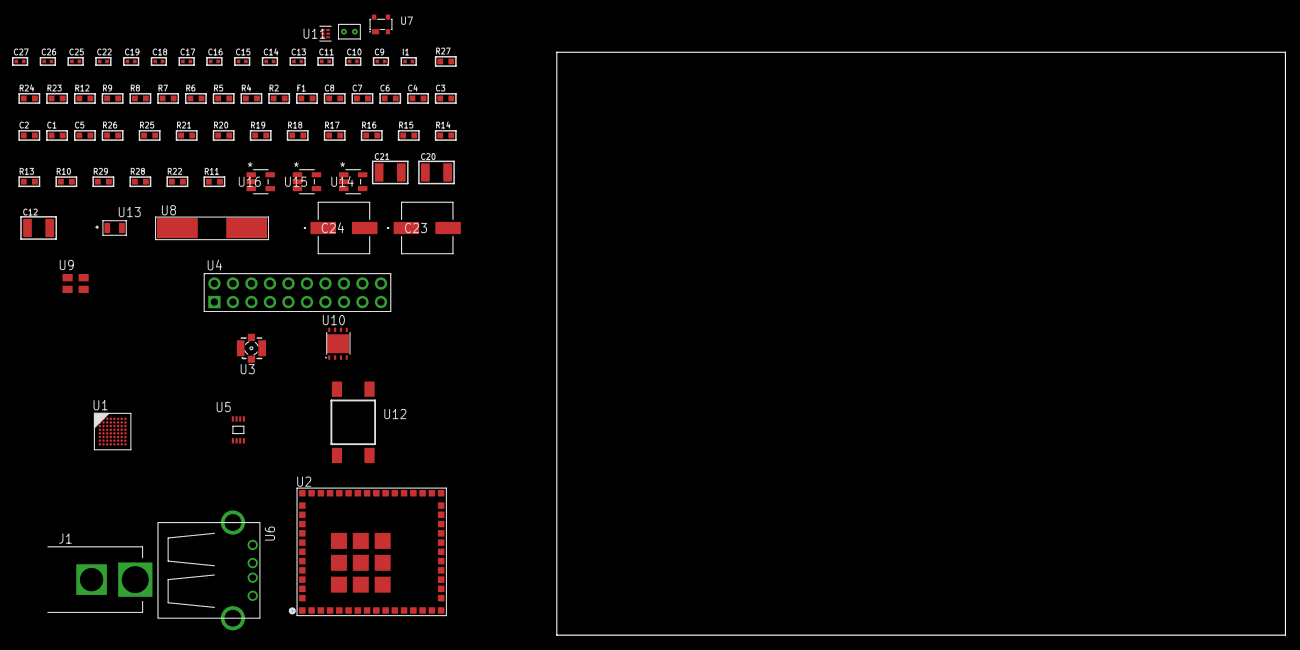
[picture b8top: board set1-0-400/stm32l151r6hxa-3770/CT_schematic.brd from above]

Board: 2 copper layers, 100.0 x 80.0 mm, 74 parts (0 on the bottom side), 40 nets, no tracks yet.

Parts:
C1, C2, C3, C4, C6: 1e-07; C0603
C5: 4.7e-06; C0603
C7: 1e-08; C0603
C8: 1e-06; C0603
C9, C10: 1e-11; C0402
C11: 1e-12; C0402
C12: 2.2e-05; C1210
C13, C14, C15, C16, C22: 1e-07; C0402
C17, C18, C19, C25, C26, C27: 1e-08; C0402
C20, C21: 1e-05; C1210
C23, C24: 0.0001; EXV-9H
F1: 240.0; L0603
I1: 3.6e-09; C0402
J1: PJ-037B; PJ-037B_PACKAGE
R2, R24: 1000.0; R0603
R4, R5: 4700.0; R0603
R6, R7, R8, R9: 2200.0; R0603
R10, R13, R14, R15, R16, R17, R18, R19, R20, R21, R25, R26: 10000.0; R0603
R11, R22: 100000.0; R0603
R12: 2700.0; R0603
R23: 2231.0; R0603
R27: 9100.0; R0603
R28: 680000.0; R0603
R29: 120000.0; R0603
U1: STM32L151R6H6A; TFBGA64
U2: CC3200MODR1M2AMOBT; LGA63S127P16X13_2050X1750X150
U3: 73412-0114; COAXIAL_C
U4: TST-110-05-T-D-RA
U5: 24AA32AT-I/MNY; TDFN-8/6MM
U6: 61400416021; USB-A-H
U7: prtr5v0u2ax; SOT143B
U8: ABLS-25.000MHZ-B2F-T
U9: ASEK-32.768KHz-ECST; ASEK
U10: LP3878SDX-ADJ/NOPB; WSON-8
U11: TPS3895ADRYR; SON-6
U12: 4-1437565-2; SW_4-1437565-2
U13: Q65110A2395; LGM67K-G1J2-24-Z
U14, U15, U16: nc7sz125m5x; NC7SZ125M5X
U17: Dummy; DUMMY_PACKAGE_165

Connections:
CLK_CRYSTAL_U1_C1: C9.1, U1.C1, U8.1
CLK_CRYSTAL_U1_D1: C10.1, U1.D1, U8.2
CLK_U1_A1: U1.A1, U9.3
GND: C1.2, C2.2, C3.2, C4.2, C5.2, C6.2, C7.2, C8.2, C9.2, C10.2, C11.2, C12.2, C13.2, C14.2, C15.2, C16.2, C17.2, C18.2, C19.2, C20.2, C21.2, C22.2, C23.2, C24.2, C25.2, C26.2, C27.2, J1.2, R2.2, R10.2, R11.2, R12.2, R18.2, R20.2, R24.2, R27.2, R29.2, U1.C2, U1.D4, U1.D5, U1.D6, U1.F1, U2.1, U2.2, U2.16, U2.27, U2.28, U2.30, U2.32, U2.38, U2.43, U2.55, U2.56, U2.57, U2.58, U2.59, U2.60, U2.61, U2.62, U2.63, U3.1, U3.2, U3.3, U3.4, U4.4, U4.6, U4.8, U4.10, U4.12, U4.14, U4.16, U4.18, U4.20, U5.4, U5.7, U6.4, U6.5, U6.6, U7.1, U9.2, U10.3, U10.PAD, U11.2, U13.C, U14.2, U14.3, U15.1, U15.3, U16.1, U16.3, U17.1
NET_U1_A3: R7.1, U1.A3, U2.4
NET_U1_B2: C6.1, U1.B2
NET_U1_B3: R6.1, U1.B3, U2.3
NET_U1_B4: R10.1, U1.B4
NET_U1_E1: R5.1, U1.E1, U16.4
NET_U1_G7: R8.1, U1.G7, U5.6
NET_U1_H1: C7.1, C8.1, F1.1, U1.G1, U1.H1
NET_U1_H7: R9.1, U1.H7, U5.5
NET_U1_H8: U12.3, U12.4
NET_U2_21: R11.1, U2.21
NET_U2_23: R12.1, U2.23
NET_U2_35: R4.1, U2.35, U15.4
NET_U3_1: C11.1, I1.1, U3.1
NET_U4_19: R18.1, U4.19
NET_U5_1: R19.1, U5.1
NET_U5_2: R20.1, U5.2
NET_U5_3: R21.1, U5.3
NET_U7_4: U6.1, U7.4
NET_U10_1: C19.1, U10.1
NET_U10_6: R23.2, R24.1, U10.6
NET_U10_8: R22.1, U10.8
NET_U11_1: R26.1, R27.1, U11.1
NET_U11_3: R28.2, R29.1, U11.3
NET_U11_4: R25.1, U11.4, U14.4, U15.2, U16.2
NET_U12_1: R2.1, U12.1, U12.2
PROC_DAC_OUT2: U1.F4, U17.2
PROC_SYS_JTCK_SWCLK: R16.1, U1.A7, U4.9
PROC_SYS_JTDI: R14.1, U1.A6, U4.5
PROC_SYS_JTDO_TRACESWO: U1.A5, U4.13
PROC_SYS_JTMS_SWDIO: R15.1, U1.A8, U4.7
PROC_SYS_JTRST: R13.1, U1.A4, U4.3
PROC_USB_DM: U1.C8, U6.2, U7.3
PROC_USB_DP: U1.B8, U6.3, U7.2
RST_OUT_U4_SRESET_B: R17.1, U4.15, U14.1
VCC_S1_12V7: C20.1, C23.1, C24.1, J1.1, R22.2, U10.4
VCC_TIER1_3V3: C1.1, C2.1, C3.1, C4.1, C5.1, C12.1, C13.1, C14.1, C15.1, C16.1, C17.1, C18.1, C21.1, C22.1, C25.1, C26.1, C27.1, F1.2, R4.2, R5.2, R6.2, R7.2, R8.2, R9.2, R13.2, R14.2, R15.2, R16.2, R17.2, R19.2, R21.2, R23.1, R25.2, R26.2, R28.1, U1.D2, U1.E4, U1.E5, U1.E6, U2.36, U2.37, U2.40, U4.1, U4.2, U5.8, U9.4, U10.5, U11.6, U14.5, U15.5, U16.5
